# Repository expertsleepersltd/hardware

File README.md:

Please see individual folders for licensing information.

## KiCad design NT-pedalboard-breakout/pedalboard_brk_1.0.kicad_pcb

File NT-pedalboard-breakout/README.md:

disting NT Pedalboard Breakout
=====

Copyright (c) 2024 Expert Sleepers Ltd

Please refer to [LICENSE.md](LICENSE.md) for licensing information.

Please note that Expert Sleepers® is a registered trade mark in the UK, the EU, and the USA. Remove any branding before making a derivative work.

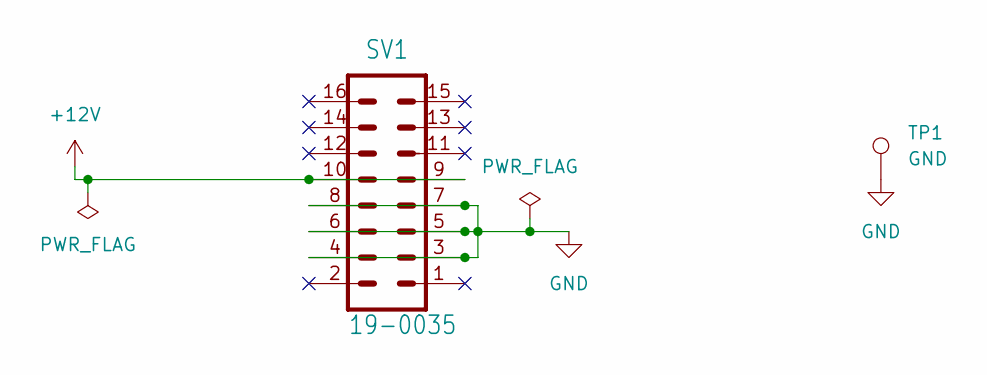
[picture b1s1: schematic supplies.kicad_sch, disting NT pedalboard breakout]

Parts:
SV1: 19-0035; ML16
TP1: GND; TestPoint_THTPad_D1.5mm_Drill0.7mm

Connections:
+12V: SV1.9, SV1.10; also elsewhere on the board
GND: SV1.3, SV1.4, SV1.5, SV1.6, SV1.7, SV1.8, TP1.1; also elsewhere on the board

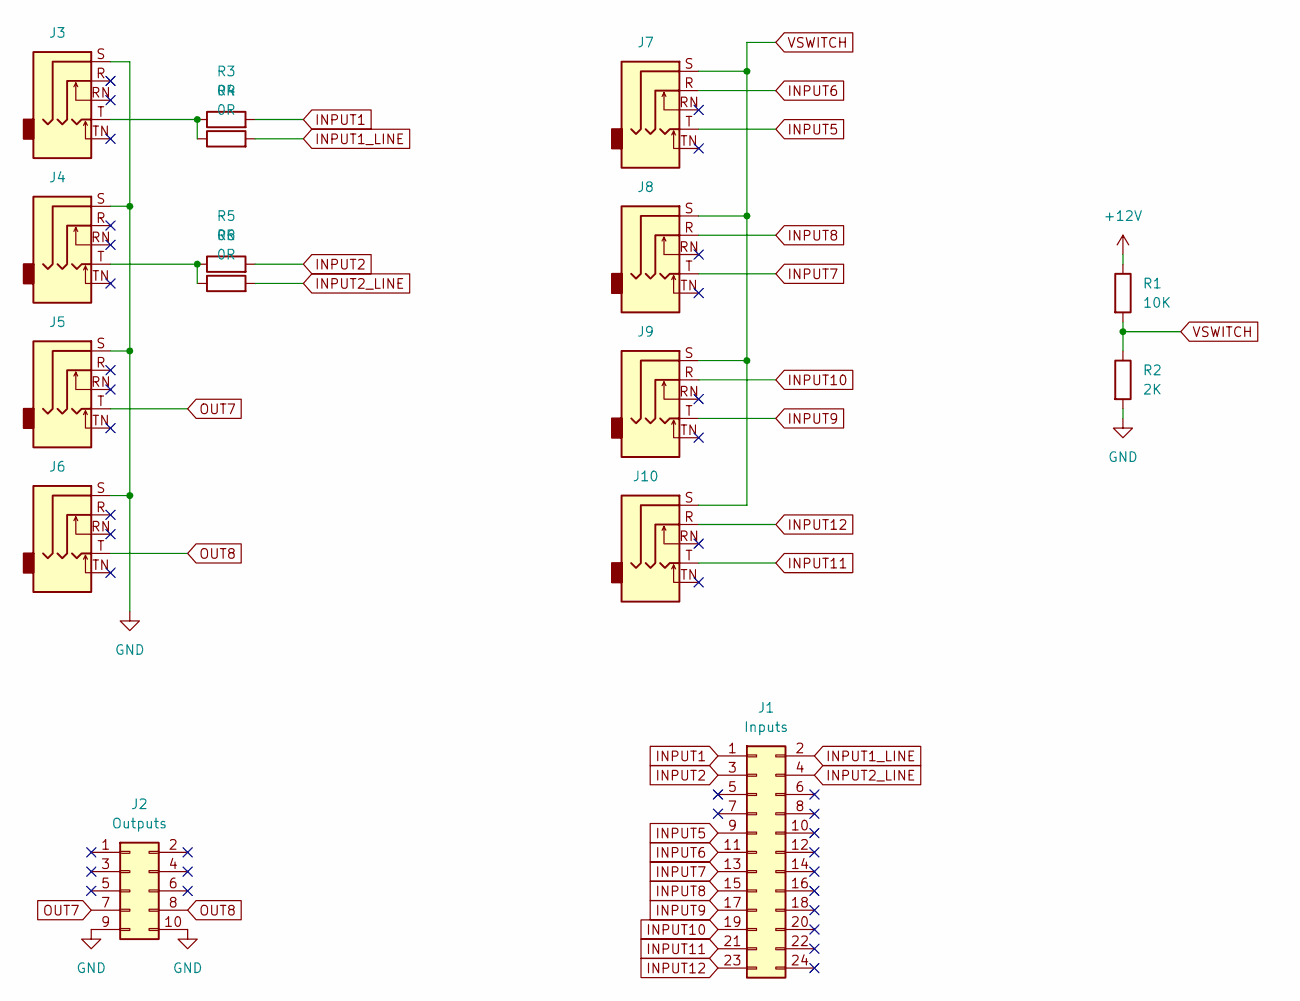
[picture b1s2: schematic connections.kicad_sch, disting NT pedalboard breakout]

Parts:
J1: Inputs; PinHeader_2x12_P2.54mm_Vertical
J2: Outputs; PinHeader_2x05_P2.54mm_Vertical
J3, J4, J5, J6, J7, J8, J9, J10: PJ612A-A
R1: 10K; R_1206_3216Metric
R2: 2K; R_1206_3216Metric
R3, R4, R5, R6: 0R; R_1206_3216Metric

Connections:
+12V: R1.1; also elsewhere on the board
GND: J2.9, J2.10, J3.S, J4.S, J5.S, J6.S, R2.2; also elsewhere on the board
INPUT1: J1.1, R3.2
INPUT1_LINE: J1.2, R4.2
INPUT2: J1.3, R5.2
INPUT2_LINE: J1.4, R6.2
INPUT5: J1.9, J7.T
INPUT6: J1.11, J7.R
INPUT7: J1.13, J8.T
INPUT8: J1.15, J8.R
INPUT9: J1.17, J9.T
INPUT10: J1.19, J9.R
INPUT11: J1.21, J10.T
INPUT12: J1.23, J10.R
unnamed: J3.T, R3.1, R4.1
unnamed: J4.T, R5.1, R6.1
OUT7: J2.7, J5.T
OUT8: J2.8, J6.T
VSWITCH: J7.S, J8.S, J9.S, J10.S, R1.2, R2.1

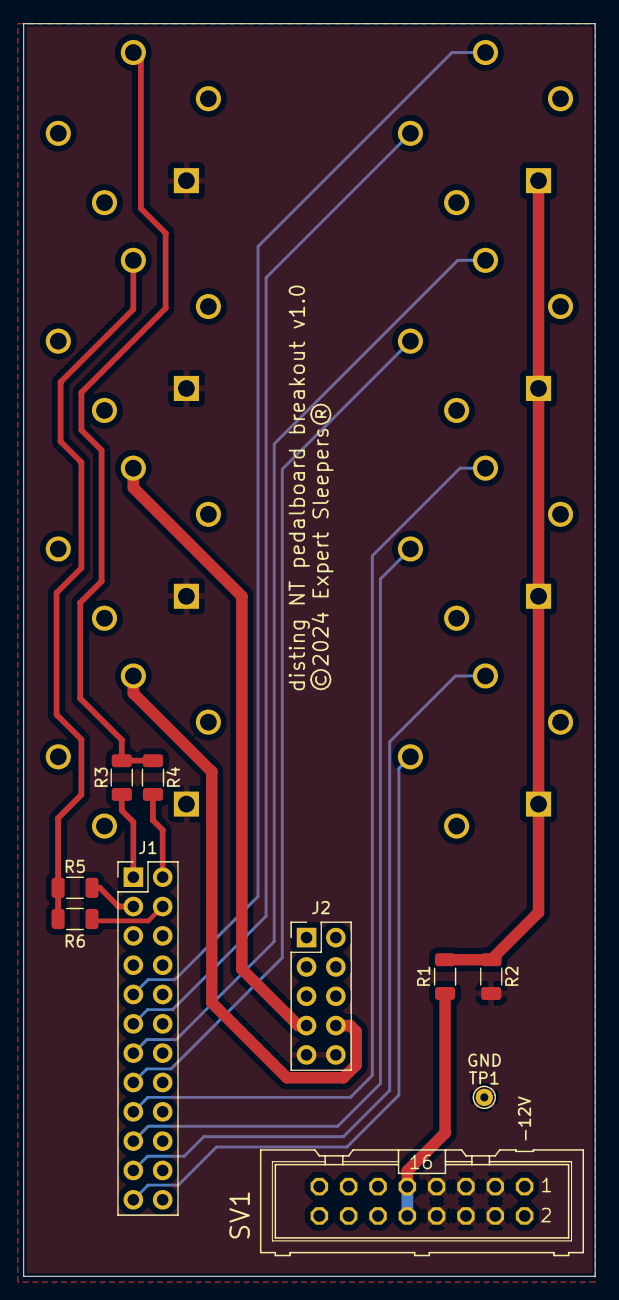
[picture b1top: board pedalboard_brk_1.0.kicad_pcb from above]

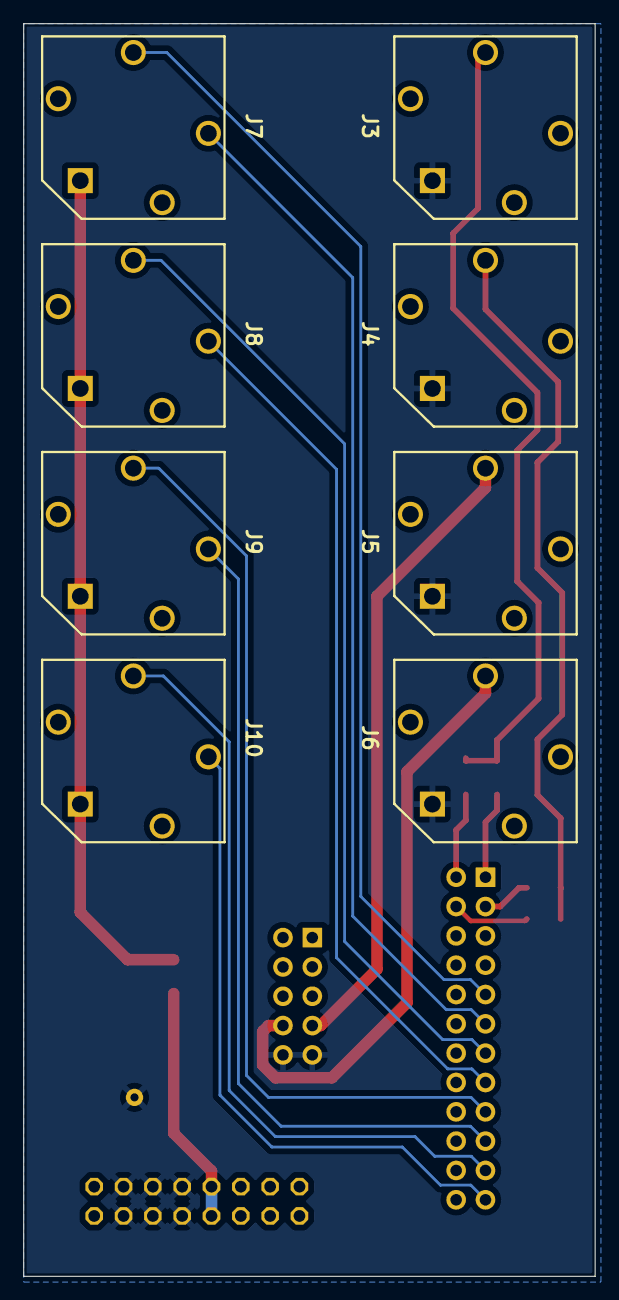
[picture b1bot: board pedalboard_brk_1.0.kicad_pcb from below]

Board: 2 copper layers, 49.5 x 108.5 mm, 18 parts (8 on the bottom side), 19 nets.

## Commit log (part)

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2021-06-18 Update README.md
    Added CC BY-SA 4.0
2021-06-24 added panels folder
2021-06-24 Update LICENSE.md
    Fixed formatting.
2021-06-24 Update README.md
    Made LICENSE.md a link to the license.
2021-06-24 added more panels
2021-06-24 renamed FH-2 to fh-2 for consistency
2021-06-24 Added the MIDI breakout
2021-07-01 added Tiny MIDI breakout
2021-09-08 Create esx-8cv-3hp.fpd
    3HP version of the FHX/ESX panel (contributed by Winter Cyan)
2021-09-08 Create esx-8cv-3hp.fpd
    3HP version of the ESX/FHX panel (contributed by Winter Cyan)
2021-09-08 3HP version of the ESX/FHX panel (contributed by Winter Cyan)
2021-10-11 added Ivo, Lorelei and Beatrix panels
2021-10-11 Added Ivo, Lorelei and Beatrix
2021-10-11 fixed READMEs which had somehow become swapped
2021-12-04 added disting mk2 panel
2021-12-15 Added Power Bus.
2022-05-20 Added 1U Display Adaptor
2022-06-09 typo
2022-06-09 Set theme jekyll-theme-slate
2022-06-09 Added disting_ex_display_connection.jpg
2022-06-15 Added css and link to forum
2022-06-30 Add power specs
2022-07-29 Added Persephone
2022-07-29 Fixed links to panels folder
2022-07-29 Added Persephone front panel
2022-11-22 added Pandora
2023-03-02 added Amelia
2023-03-13 Added link to Thonk
2023-07-12 added Aloysius
2023-09-26 Added Cicely
2024-02-26 Added Otterley.
2024-05-20 Added FH-1
2024-11-22 added disting NT panel
2024-12-09 Added disting NT pedablboard breakout
2026-06-03 Added NTX-8CV panel

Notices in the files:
NT-pedalboard-breakout/pedalboard_brk_1.0.kicad_pcb:
©2024 Expert Sleepers®
